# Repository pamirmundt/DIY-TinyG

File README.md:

# DIY TinyG
## DIY TinyG with Original Dimensions
This version has the original board dimensions and connector positions. 1206 package is selected for resistors and caps for easy hand soldering. Other than board dimensions and connector positions, rest of the components' positions are not exact.

- [X] Eagle Schmatic and Board File
- [ ] Bill of Materials
- [ ] Tested and Working

## DIY TinyG with Optimised Dimensions (100x100mm)
This version does **not** have the original board dimensions and connector positions. There is a relatively big price difference between *105x101mm* and *100x100mm* board dimensions at Seeed, OSH, JLCPCB and etc. So this version is a bit trimmed.

- [ ] Eagle Schmatic and Board File
- [ ] Bill of Materials
- [ ] Tested and Working

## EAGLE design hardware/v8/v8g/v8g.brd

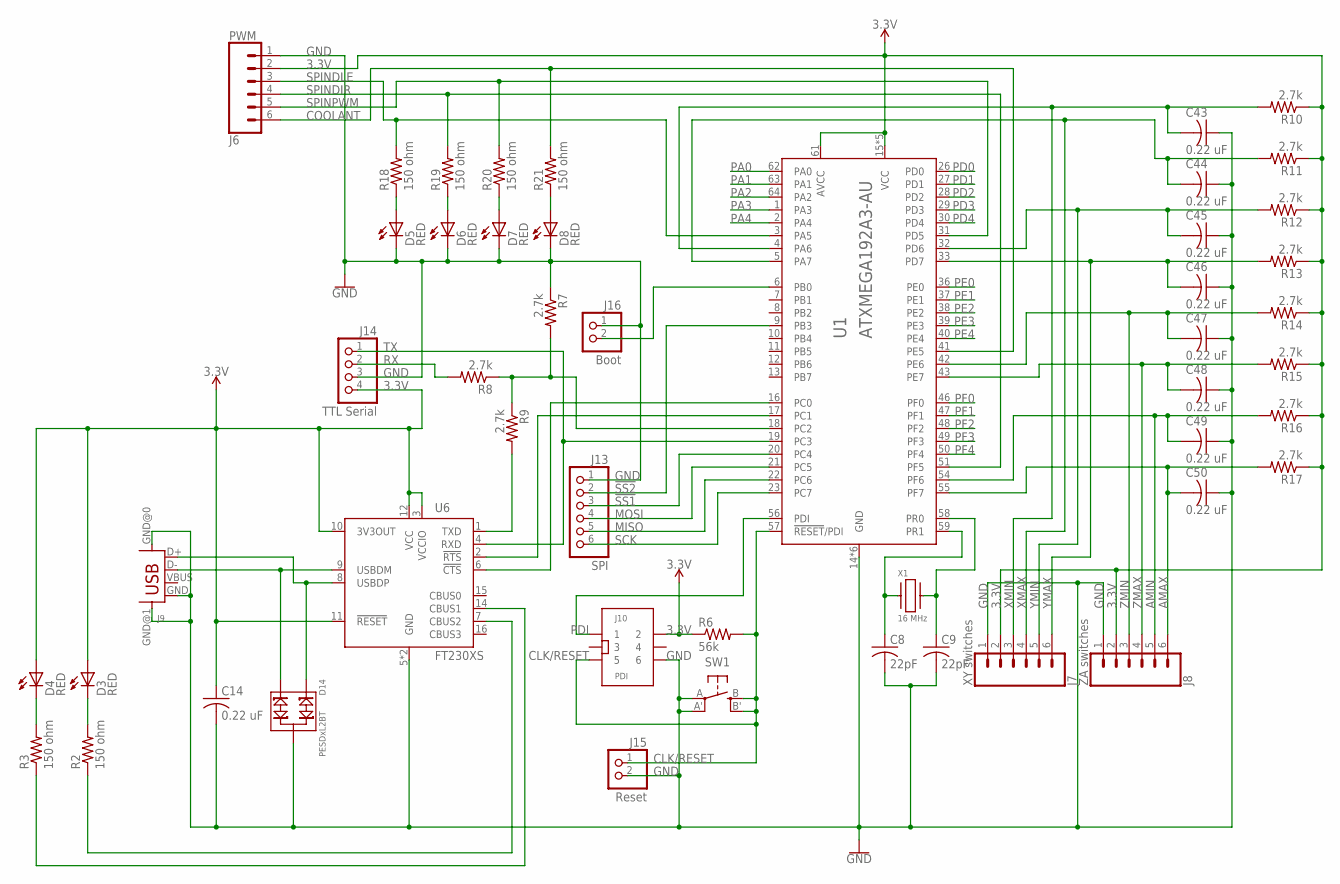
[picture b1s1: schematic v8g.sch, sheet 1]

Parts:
C8, C9: 22pF; C1206
C14, C43, C44, C45, C46, C47, C48, C49, C50: 0.22 uF; C1206
D3, D4, D5, D6, D7, D8: RED; CHIPLED_1206
D14: PESDxL2BT; SOT23
J6: PWM; SCREWTERMINAL-3.5MM-6
J7: XY switches; SCREWTERMINAL-3.5MM-6
J8: ZA switches; SCREWTERMINAL-3.5MM-6
J9: USB; USB-B-H
J10: PDI; IDC-6-PIN-61200621621
J13: SPI; 1X06
J14: TTL Serial; 1X04
J15: Reset; 1X02
J16: Boot; 1X02
R2, R3, R18, R19, R20, R21: 150 ohm; M1206
R6: 56k; M1206
R7, R8, R9, R10, R11, R12, R13, R14, R15, R16, R17: 2.7k; M1206
SW1: SPST_TACT-EVQQ2; EVQ-Q2
U1: ATXMEGA192A3-AU; TQFP-64A-64
U6: FT230XS; SSOP16
X1: 16 MHz; C4ST-SMD

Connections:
3.3V: C14.1, D3.A, D4.A, J6.2, J7.2, J8.2, J10.2, J14.4, R6.1, R10.1, R11.1, R12.1, R13.1, R14.1, R15.1, R16.1, R17.1, U1.15 (VCC), U1.25 (VCC), U1.35 (VCC), U1.45 (VCC), U1.53 (VCC), U1.61 (AVCC), U6.3 (VCCIO), U6.10 (3V3OUT), U6.11 (!RESET), U6.12 (VCC); also elsewhere on the board
!SS1: J13.3, U1.20 (PC4)
!SS2: J13.2, U1.9 (PB3)
AMAX: C50.2, J8.6, R17.2, U1.55 (PF7)
AMIN: C49.2, J8.5, R16.2, U1.54 (PF6)
CLK/RESET: J10.5, J15.1, R6.2, SW1.B (S), SW1.B' (S1), U1.57 (!RESET!/PDI)
COOLANT: J6.6, R21.2, U1.41 (PE5)
GND: C8.2, C9.2, C14.2, C43.1, C44.1, C45.1, C46.1, C47.1, C48.1, C49.1, C50.1, D5.C, D6.C, D7.C, D8.C, D14.3, J6.1, J7.1, J8.1, J9.GND, J9.GND@0 (GND), J9.GND@1 (GND), J10.6, J13.1, J14.3, J15.2, J16.1, R7.1, SW1.A, SW1.A' (P1), U1.14 (GND), U1.24 (GND), U1.34 (GND), U1.44 (GND), U1.52 (GND), U1.60 (GND), U6.5 (GND), U6.13 (GND); also elsewhere on the board
MISO: J13.5, U1.22 (PC6)
MOSI: J13.4, U1.21 (PC5)
unnamed: R9.2, U6.1 (TXD)
unnamed: D14.2, J9.D-, U6.9 (USBDM)
unnamed: R3.1, U6.14 (CBUS1)
unnamed: J16.2, U1.6 (PB0)
unnamed: D5.A, R18.1
unnamed: D6.A, R19.1
unnamed: D7.A, R20.1
unnamed: D8.A, R21.1
unnamed: R2.1, U6.7 (CBUS2)
unnamed: U1.16 (PC0), U6.6 (!CTS)
unnamed: U1.17 (PC1), U6.2 (!RTS)
unnamed: R7.2, R8.1, R9.1, U1.18 (PC2)
unnamed: D14.1, J9.D+, U6.8 (USBDP)
unnamed: D3.C, R2.2
unnamed: D4.C, R3.2
unnamed: C8.1, U1.59 (PR1), X1.1
unnamed: C9.1, U1.58 (PR0), X1.2
PA0: U1.62 (PA0); also elsewhere on the board
PA1: U1.63 (PA1); also elsewhere on the board
PA2: U1.64 (PA2); also elsewhere on the board
PA3: U1.1 (PA3); also elsewhere on the board
PA4: U1.2 (PA4); also elsewhere on the board
PD0: U1.26 (PD0); also elsewhere on the board
PD1: U1.27 (PD1); also elsewhere on the board
PD2: U1.28 (PD2); also elsewhere on the board
PD3: U1.29 (PD3); also elsewhere on the board
PD4: U1.30 (PD4); also elsewhere on the board
PDI: J10.1, U1.56 (PDI)
PE0: U1.36 (PE0); also elsewhere on the board
PE1: U1.37 (PE1); also elsewhere on the board
PE2: U1.38 (PE2); also elsewhere on the board
PE3: U1.39 (PE3); also elsewhere on the board
PE4: U1.40 (PE4); also elsewhere on the board
PF0: U1.46 (PF0); also elsewhere on the board
PF1: U1.47 (PF1); also elsewhere on the board
PF2: U1.48 (PF2); also elsewhere on the board
PF3: U1.49 (PF3); also elsewhere on the board
PF4: U1.50 (PF4); also elsewhere on the board
RX: J14.2, R8.2
SCK: J13.6, U1.23 (PC7)
SPINDIR: J6.4, R19.2, U1.51 (PF5)
SPINDLE: J6.3, R18.2, U1.3 (PA5)
SPINPWM: J6.5, R20.2, U1.31 (PD5)
TX: J14.1, U1.19 (PC3), U6.4 (RXD)
XMAX: C44.2, J7.4, R11.2, U1.5 (PA7)
XMIN: C43.2, J7.3, R10.2, U1.4 (PA6)
YMAX: C46.2, J7.6, R13.2, U1.33 (PD7)
YMIN: C45.2, J7.5, R12.2, U1.32 (PD6)
ZMAX: C48.2, J8.4, R15.2, U1.43 (PE7)
ZMIN: C47.2, J8.3, R14.2, U1.42 (PE6)

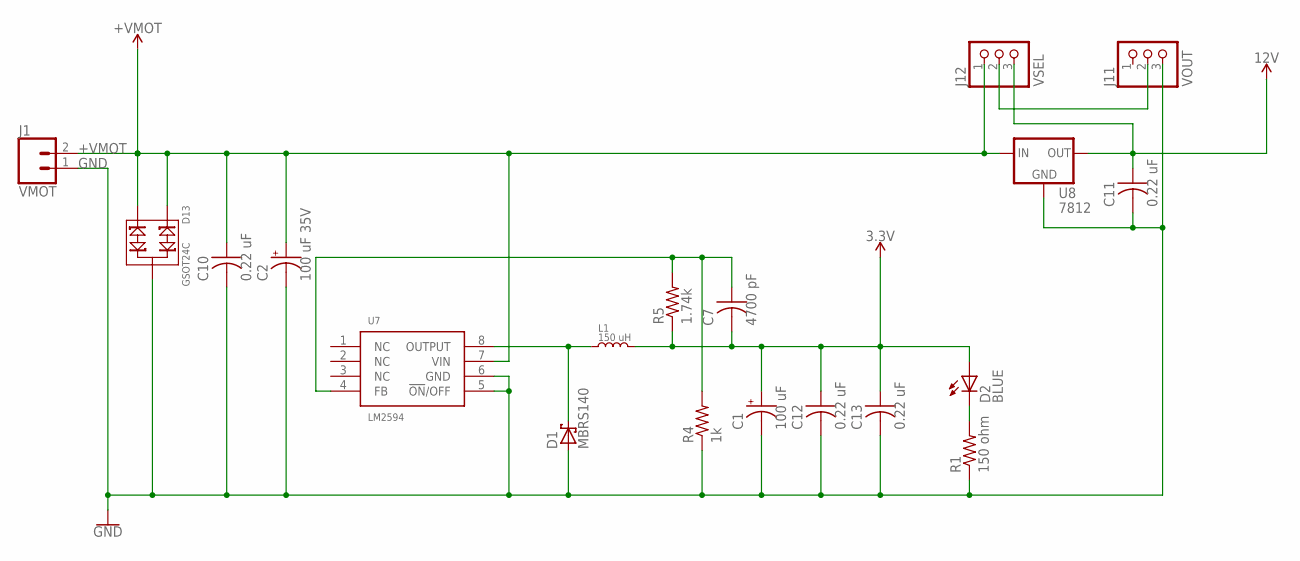
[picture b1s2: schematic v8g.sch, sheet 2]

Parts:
C1: 100 uF; WCAP-ASLI
C2: 100 uF 35V; WCAP-ASLI
C7: 4700 pF; C1206
C10, C11, C12, C13: 0.22 uF; C1206
D1: MBRS140; DO-214AA
D2: BLUE; CHIPLED_1206
D13: GSOT24C; SOT23
J1: VMOT; SCREWTERMINAL-5MM-2
J11: VOUT; 1X03
J12: VSEL; 1X03
L1: 150 uH; SDE0805A
R1: 150 ohm; R1206
R4: 1k; R1206
R5: 1.74k; R1206
U7: LM2594; SOIC-8_NB
U8: 7812; D2PAK

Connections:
3.3V: C1.+, C7.2, C12.1, C13.1, D2.A, L1.2, R5.1; also elsewhere on the board
12V: C11.1, J12.3, U8.3 (OUT)
+VMOT: C2.+, C10.1, D13.1, D13.2, J1.2, J12.1, U7.7 (VIN), U8.1 (IN); also elsewhere on the board
GND: C1.-, C2.-, C10.2, C11.2, C12.2, C13.2, D1.A, D13.3, J1.1, J11.3, R1.1, R4.1, U7.5 (!ON!/OFF), U7.6 (GND), U8.2 (GND); also elsewhere on the board
unnamed: D2.C, R1.2
unnamed: J11.2, J12.2
unnamed: D1.C, L1.1, U7.8 (OUTPUT)
unnamed: C7.1, R4.2, R5.2, U7.4 (FB)

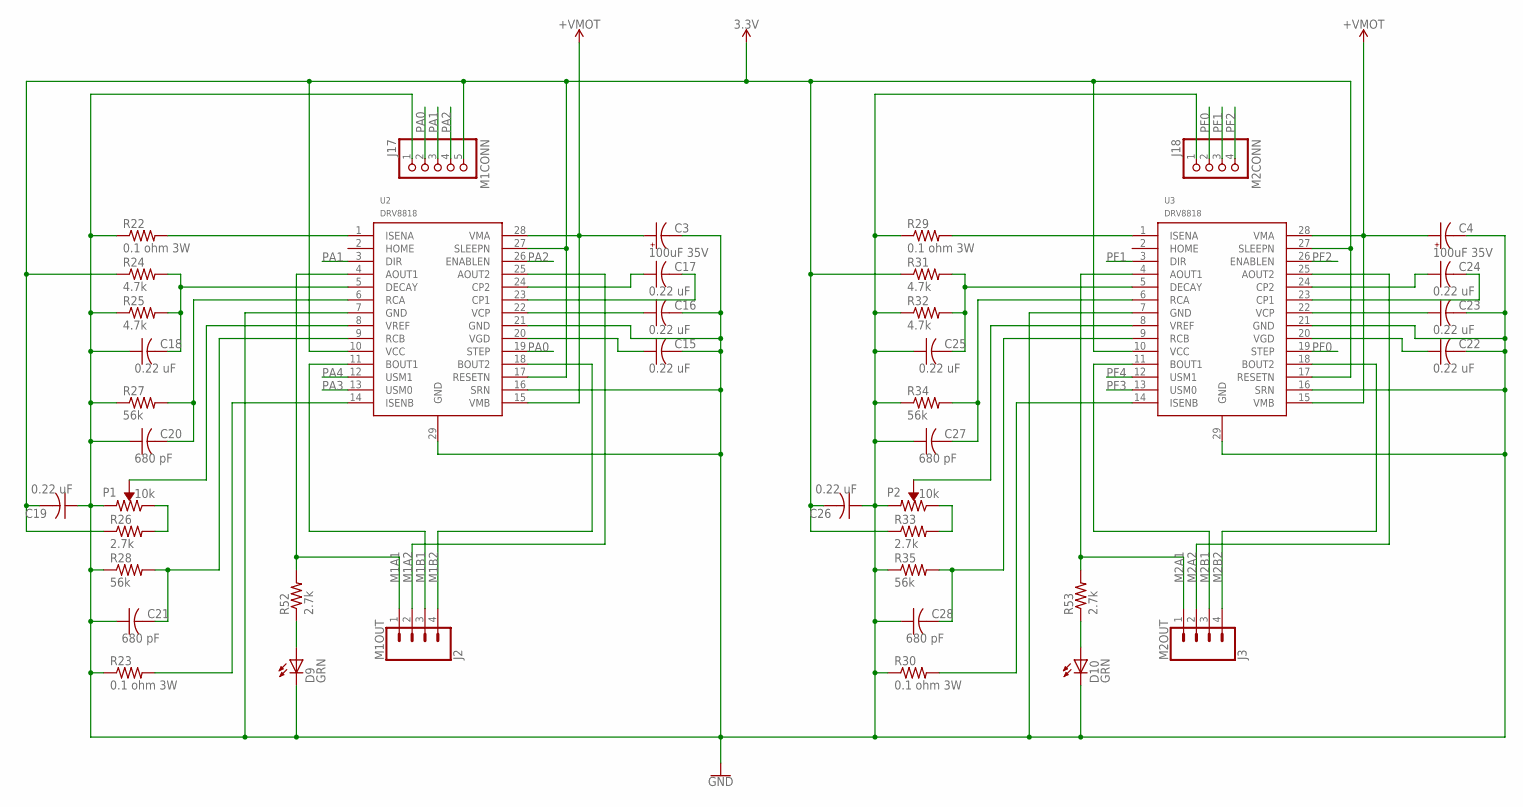
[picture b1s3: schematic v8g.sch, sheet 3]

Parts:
C3, C4: 100uF 35V; WCAP-ASLI
C15, C16, C17, C18, C19, C22, C23, C24, C25, C26: 0.22 uF; C1206
C20, C21, C27, C28: 680 pF; C1206
D9, D10: GRN; CHIPLED_1206
J2: M1OUT; SCREWTERMINAL-3.5MM-4
J3: M2OUT; SCREWTERMINAL-3.5MM-4
J17: M1CONN; 1X05
J18: M2CONN; 1X04
P1, P2: 10k; BOURNS_3361P
R22, R23, R29, R30: 0.1 ohm 3W; R2512
R24, R25, R31, R32: 4.7k; R1206
R26, R33: 2.7k; R1206
R27, R28, R34, R35: 56k; R1206
R52, R53: 2.7k; 0207/7
U2, U3: DRV8818; HTSSOP_28-PIN

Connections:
3.3V: C19.2, C26.2, J17.5, R24.1, R26.1, R31.1, R33.1, U2.10 (VCC), U2.17 (RESETN), U2.27 (SLEEPN), U3.10 (VCC), U3.17 (RESETN), U3.27 (SLEEPN); also elsewhere on the board
+VMOT: C3.+, C4.+, U2.15 (VMB), U2.28 (VMA), U3.15 (VMB), U3.28 (VMA); also elsewhere on the board
GND: C3.-, C4.-, C15.2, C16.2, C18.1, C19.1, C20.1, C21.1, C22.2, C23.2, C25.1, C26.1, C27.1, C28.1, D9.C, D10.C, J17.1, J18.1, P1.1, P2.1, R22.1, R23.1, R25.1, R27.1, R28.1, R29.1, R30.1, R32.1, R34.1, R35.1, U2.7 (GND), U2.16 (SRN), U2.21 (GND), U2.29 (GND), U3.7 (GND), U3.16 (SRN), U3.21 (GND), U3.29 (GND); also elsewhere on the board
M1A1: J2.1, R52.2, U2.4 (AOUT1)
M1A2: J2.2, U2.25 (AOUT2)
M1B1: J2.3, U2.11 (BOUT1)
M1B2: J2.4, U2.18 (BOUT2)
M2A1: J3.1, R53.2, U3.4 (AOUT1)
M2A2: J3.2, U3.25 (AOUT2)
M2B1: J3.3, U3.11 (BOUT1)
M2B2: J3.4, U3.18 (BOUT2)
unnamed: D9.A, R52.1
unnamed: R22.2, U2.1 (ISENA)
unnamed: P1.2, U2.8 (VREF)
unnamed: C17.1, U2.24 (CP2)
unnamed: P1.3, R26.2
unnamed: C17.2, U2.23 (CP1)
unnamed: C18.2, R24.2, R25.2, U2.5 (DECAY)
unnamed: C20.2, R27.2, U2.6 (RCA)
unnamed: C21.2, R28.2, U2.9 (RCB)
unnamed: R23.2, U2.14 (ISENB)
unnamed: C16.1, U2.22 (VCP)
unnamed: C15.1, U2.20 (VGD)
unnamed: R29.2, U3.1 (ISENA)
unnamed: C25.2, R31.2, R32.2, U3.5 (DECAY)
unnamed: C27.2, R34.2, U3.6 (RCA)
unnamed: P2.2, U3.8 (VREF)
unnamed: P2.3, R33.2
unnamed: C28.2, R35.2, U3.9 (RCB)
unnamed: R30.2, U3.14 (ISENB)
unnamed: D10.A, R53.1
unnamed: C24.2, U3.23 (CP1)
unnamed: C23.1, U3.22 (VCP)
unnamed: C22.1, U3.20 (VGD)
unnamed: C24.1, U3.24 (CP2)
PA0: J17.2, U2.19 (STEP); also elsewhere on the board
PA1: J17.3, U2.3 (DIR); also elsewhere on the board
PA2: J17.4, U2.26 (ENABLEN); also elsewhere on the board
PA3: U2.13 (USM0); also elsewhere on the board
PA4: U2.12 (USM1); also elsewhere on the board
PF0: J18.2, U3.19 (STEP); also elsewhere on the board
PF1: J18.3, U3.3 (DIR); also elsewhere on the board
PF2: J18.4, U3.26 (ENABLEN); also elsewhere on the board
PF3: U3.13 (USM0); also elsewhere on the board
PF4: U3.12 (USM1); also elsewhere on the board

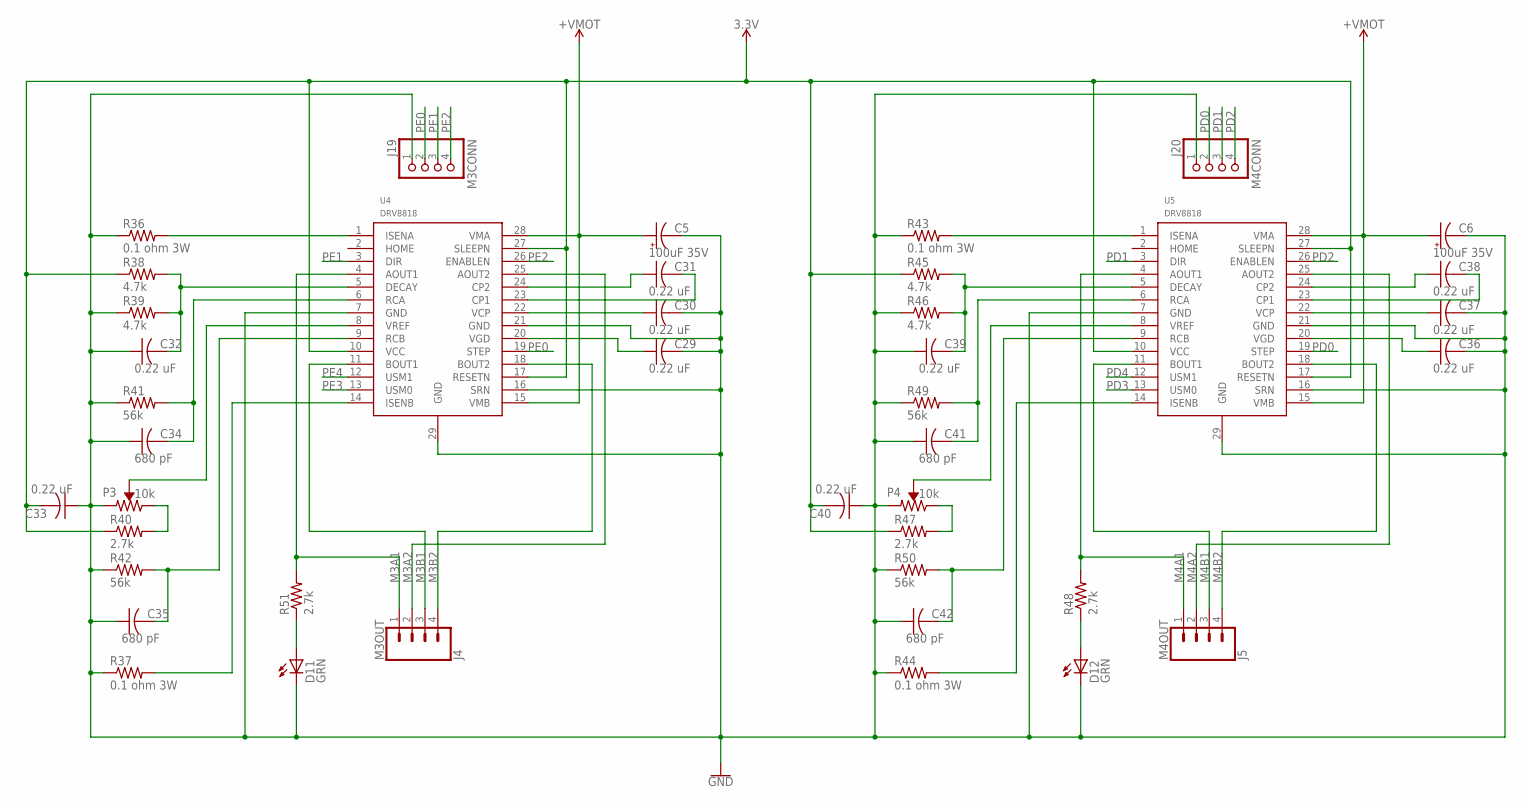
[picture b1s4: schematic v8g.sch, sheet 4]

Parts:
C5, C6: 100uF 35V; WCAP-ASLI
C29, C30, C31, C32, C33, C36, C37, C38, C39, C40: 0.22 uF; C1206
C34, C35, C41, C42: 680 pF; C1206
D11, D12: GRN; CHIPLED_1206
J4: M3OUT; SCREWTERMINAL-3.5MM-4
J5: M4OUT; SCREWTERMINAL-3.5MM-4
J19: M3CONN; 1X04
J20: M4CONN; 1X04
P3, P4: 10k; BOURNS_3361P
R36, R37, R43, R44: 0.1 ohm 3W; R2512
R38, R39, R45, R46: 4.7k; R1206
R40, R47: 2.7k; R1206
R41, R42, R49, R50: 56k; R1206
R48, R51: 2.7k; 0207/7
U4, U5: DRV8818; HTSSOP_28-PIN

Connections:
3.3V: C33.2, C40.2, R38.1, R40.1, R45.1, R47.1, U4.10 (VCC), U4.17 (RESETN), U4.27 (SLEEPN), U5.10 (VCC), U5.17 (RESETN), U5.27 (SLEEPN); also elsewhere on the board
+VMOT: C5.+, C6.+, U4.15 (VMB), U4.28 (VMA), U5.15 (VMB), U5.28 (VMA); also elsewhere on the board
GND: C5.-, C6.-, C29.2, C30.2, C32.1, C33.1, C34.1, C35.1, C36.2, C37.2, C39.1, C40.1, C41.1, C42.1, D11.C, D12.C, J19.1, J20.1, P3.1, P4.1, R36.1, R37.1, R39.1, R41.1, R42.1, R43.1, R44.1, R46.1, R49.1, R50.1, U4.7 (GND), U4.16 (SRN), U4.21 (GND), U4.29 (GND), U5.7 (GND), U5.16 (SRN), U5.21 (GND), U5.29 (GND); also elsewhere on the board
M3A1: J4.1, R51.2, U4.4 (AOUT1)
M3A2: J4.2, U4.25 (AOUT2)
M3B1: J4.3, U4.11 (BOUT1)
M3B2: J4.4, U4.18 (BOUT2)
M4A1: J5.1, R48.2, U5.4 (AOUT1)
M4A2: J5.2, U5.25 (AOUT2)
M4B1: J5.3, U5.11 (BOUT1)
M4B2: J5.4, U5.18 (BOUT2)
unnamed: R36.2, U4.1 (ISENA)
unnamed: C32.2, R38.2, R39.2, U4.5 (DECAY)
unnamed: C34.2, R41.2, U4.6 (RCA)
unnamed: P3.2, U4.8 (VREF)
unnamed: P3.3, R40.2
unnamed: C35.2, R42.2, U4.9 (RCB)
unnamed: R37.2, U4.14 (ISENB)
unnamed: D11.A, R51.1
unnamed: C31.2, U4.23 (CP1)
unnamed: C30.1, U4.22 (VCP)
unnamed: C29.1, U4.20 (VGD)
unnamed: C31.1, U4.24 (CP2)
unnamed: R43.2, U5.1 (ISENA)
unnamed: C39.2, R45.2, R46.2, U5.5 (DECAY)
unnamed: C41.2, R49.2, U5.6 (RCA)
unnamed: P4.2, U5.8 (VREF)
unnamed: P4.3, R47.2
unnamed: C42.2, R50.2, U5.9 (RCB)
unnamed: R44.2, U5.14 (ISENB)
unnamed: D12.A, R48.1
unnamed: C38.2, U5.23 (CP1)
unnamed: C37.1, U5.22 (VCP)
unnamed: C36.1, U5.20 (VGD)
unnamed: C38.1, U5.24 (CP2)
PD0: J20.2, U5.19 (STEP); also elsewhere on the board
PD1: J20.3, U5.3 (DIR); also elsewhere on the board
PD2: J20.4, U5.26 (ENABLEN); also elsewhere on the board
PD3: U5.13 (USM0); also elsewhere on the board
PD4: U5.12 (USM1); also elsewhere on the board
PE0: J19.2, U4.19 (STEP); also elsewhere on the board
PE1: J19.3, U4.3 (DIR); also elsewhere on the board
PE2: J19.4, U4.26 (ENABLEN); also elsewhere on the board
PE3: U4.13 (USM0); also elsewhere on the board
PE4: U4.12 (USM1); also elsewhere on the board

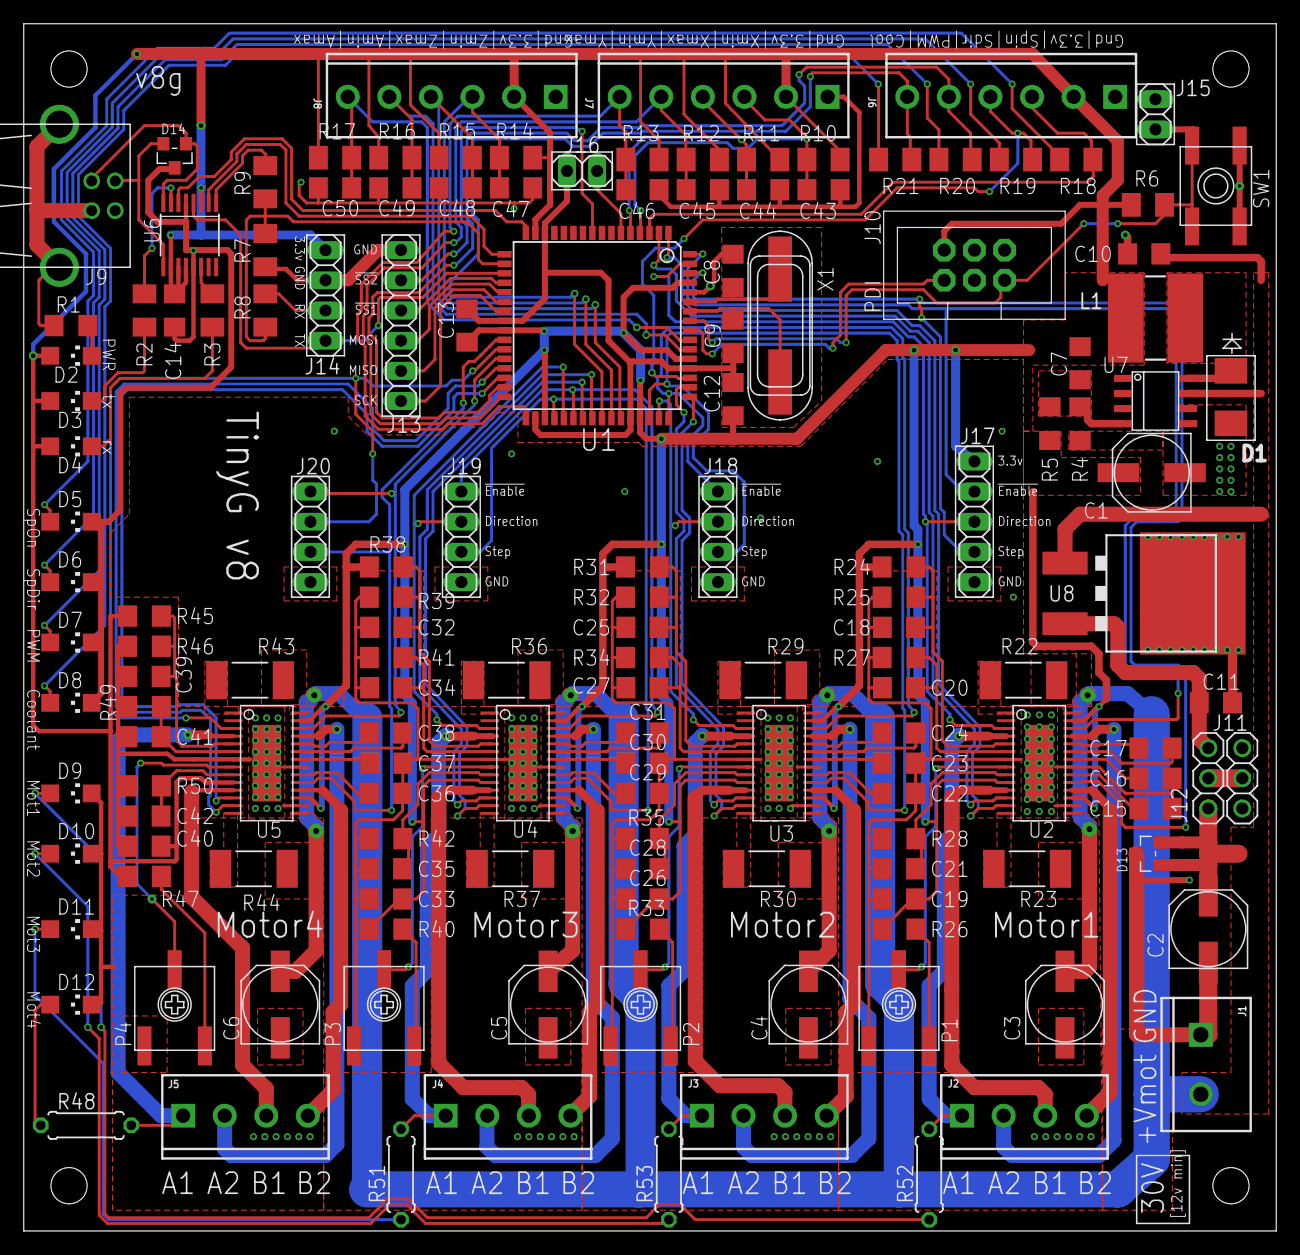
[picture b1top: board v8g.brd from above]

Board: 2 copper layers, 105.4 x 101.6 mm, 152 parts (0 on the bottom side), 130 nets.

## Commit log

2018-08-28 init commit

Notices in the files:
parts and their libraries:
SparkFun-Connectors: Licensing: Creative Commons ShareAlike 4.0 International - https://creativecommons.org/licenses/by-sa/4.0
